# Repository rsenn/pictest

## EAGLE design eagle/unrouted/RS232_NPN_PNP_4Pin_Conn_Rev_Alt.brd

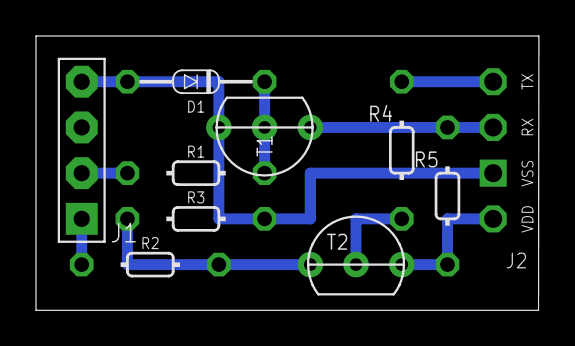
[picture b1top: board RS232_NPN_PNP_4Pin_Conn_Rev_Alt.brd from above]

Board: 2 copper layers, 27.9 x 15.2 mm, 10 parts (0 on the bottom side), 9 nets.

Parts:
D1: 1N414834-7; DO34-7
J1: COMPORT-4PIN-NEW; RS232-4PIN-NEW
J2: PIC-UART-X
R1: 10k; 0202/7
R2: 1k; 0202/7
R3: 4.7k; 0202/7
R4: 10k; 0202/7-V
R5: 1k; 0202/7-V
T1: BC547; TO92-CBE
T2: BC557; TO92-CBE

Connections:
+5V: J2.20, R5.2, T2.E
GND: D1.A, J1.4, J2.19, R3.1, T1.E
unnamed: J2.18, R5.1, T1.C
unnamed: D1.C, R1.1, T1.B
unnamed: J1.2, R1.2
unnamed: J2.17, R4.1
unnamed: R4.2, T2.B
unnamed: R2.1, R3.2, T2.C
unnamed: J1.1, R2.2

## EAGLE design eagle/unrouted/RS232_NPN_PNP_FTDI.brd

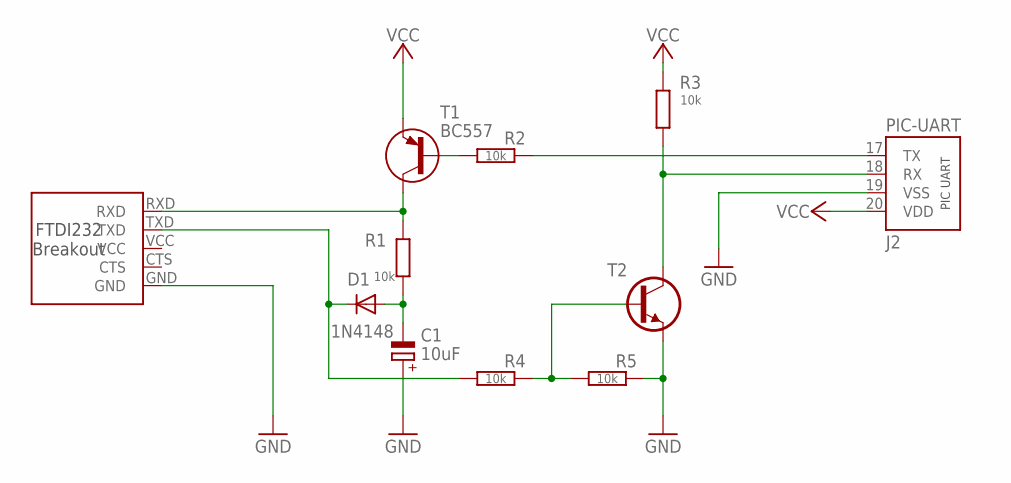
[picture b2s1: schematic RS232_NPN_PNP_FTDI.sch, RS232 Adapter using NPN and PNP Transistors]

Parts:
C1: 10uF; E5-4
D1: 1N4148; DO34-5V
J1: FTDI232-BO-5P-L; FTDI232-BO-5-L
J2: PIC-UART
R1: 10k; 0202/5-V
R2, R3, R5: 10k; 0202/7
R4: 10k; 0202/7-V
T1: BC557; TO92-CBE
T2: BC547; TO92-CBE

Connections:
-12V: C1.-, D1.A, R1.2
GND: C1.+, J1.GND, J2.19 (VSS), R5.1, T2.E
unnamed: R2.2, T1.B
unnamed: R4.1, R5.2, T2.B
RX: J2.18 (RX), R3.2, T2.C
RXD: J1.RXD, R1.1, T1.C
TX: J2.17 (TX), R2.1
TXD: D1.C, J1.TXD, R4.2
VCC: J2.20 (VDD), R3.1, T1.E

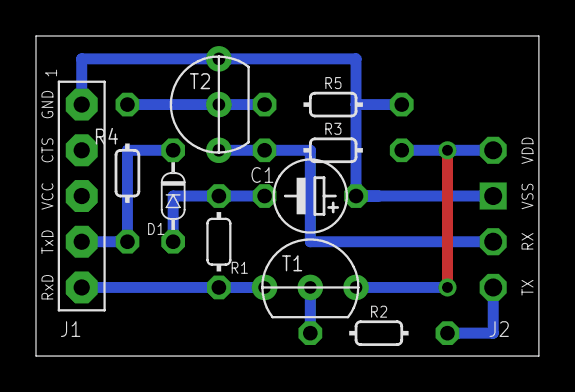
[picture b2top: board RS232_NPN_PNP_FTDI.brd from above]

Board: 2 copper layers, 27.9 x 17.8 mm, 11 parts (0 on the bottom side), 9 nets.

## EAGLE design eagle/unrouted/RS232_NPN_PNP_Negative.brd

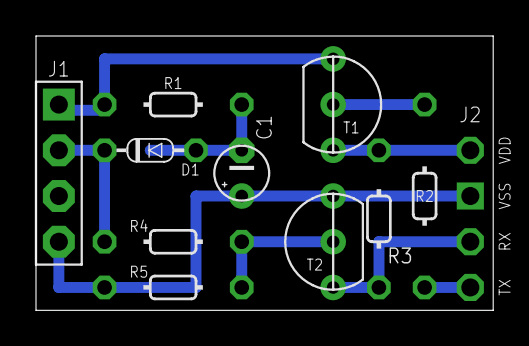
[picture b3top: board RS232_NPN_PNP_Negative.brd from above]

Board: 2 copper layers, 25.4 x 15.2 mm, 11 parts (0 on the bottom side), 9 nets.

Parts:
C1: 10uF; E2,5-3
D1: 1N4148; DO34-5
J1: COMPORT-4PIN-NEW-L; RS232-4PIN-NEW-L
J2: PIC UART (4pin); PIC-UART
R1, R4, R5: 10k; 0202/7
R2: 10k; 0202/10-V
R3: 10k; 0202/7-V
T1: BC557; TO92-CBE
T2: BC547; TO92-CBE

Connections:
-12V: C1.-, D1.A, R1.1
GND: C1.+, J1.4, J2.19, R5.2, T2.E
unnamed: R2.2, T1.B
unnamed: R4.1, R5.1, T2.B
RX: J2.18, R3.1, T2.C
RXD: J1.1, R1.2, T1.C
TX: J2.17, R2.1
TXD: D1.C, J1.2, R4.2
VCC: J2.20, R3.2, T1.E

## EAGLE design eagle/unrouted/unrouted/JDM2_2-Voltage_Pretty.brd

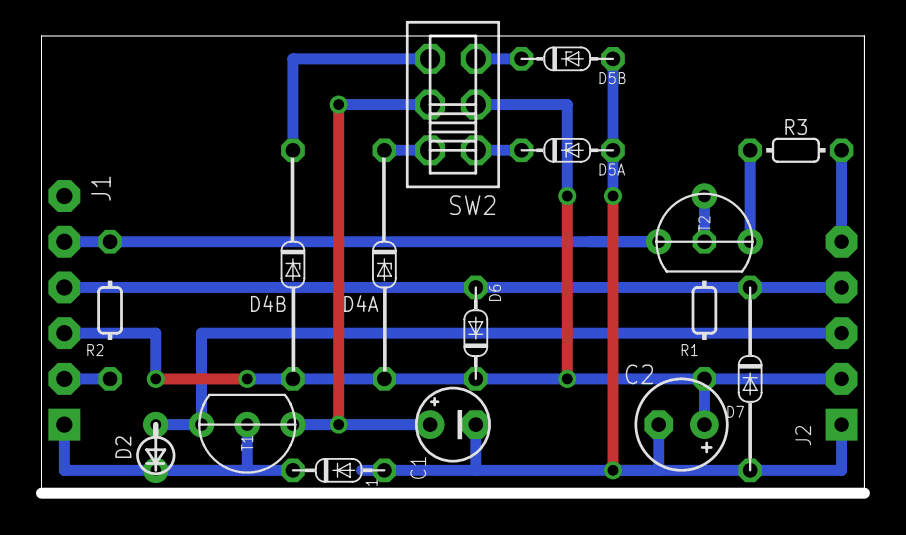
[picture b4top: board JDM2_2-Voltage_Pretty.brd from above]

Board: 2 copper layers, 45.7 x 25.4 mm, 18 parts (0 on the bottom side), 15 nets.

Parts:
C1: 100uF; E2,5-4
C2: 22uF; E2,5-5
D1: 1N4148; DO34-5V
D2: 1N4148; DO34-2,5-A
D4A: Z=5.1V; DO34Z12V
D4B: Z=8.1V; DO34Z12V
D5A: Z=3.3V; DO34Z5
D5B: Z=5.1V; DO34Z5
D6: 1N4148; DO34-5
D7: 1N4148; DO34-10V
J1: COMPORT-6PIN; RS232-6PIN
J2: PIC-ICSPICSP; PIC-ICSP
R1: 10k; 0202/7-V
R2: 1.5k; 0202/7-V
R3: 100; 0202/5
SW2: SL-SW-2P-2T-SV; SLSW-2P2T
T1: BC547; TO92-CBE
T2: BC547; TO92-CBE-A

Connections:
/MCLR: D2.A, J2.3, T1.E
CLK: D6.A, D7.C, J1.4, J2.4
CTS: J1.5, R2.1, T2.C
DATA: R3.2, T2.E
GND: C1.-, C2.-, D1.A, D5A.A, D5B.A, D7.A, J2.1
unnamed: R1.1, T2.B
unnamed: D5A.C, SW2.1
unnamed: D5B.C, SW2.3
unnamed: D4A.C, SW2.4
unnamed: D4B.C, SW2.6
unnamed: J1.2, R2.2
PGD: J2.5, R3.1
TXD: D1.C, D2.C, J1.1, T1.B
VCC: C2.+, D4A.A, D4B.A, D6.C, J1.3, J2.2, R1.2, SW2.2
VPP: C1.+, SW2.5, T1.C

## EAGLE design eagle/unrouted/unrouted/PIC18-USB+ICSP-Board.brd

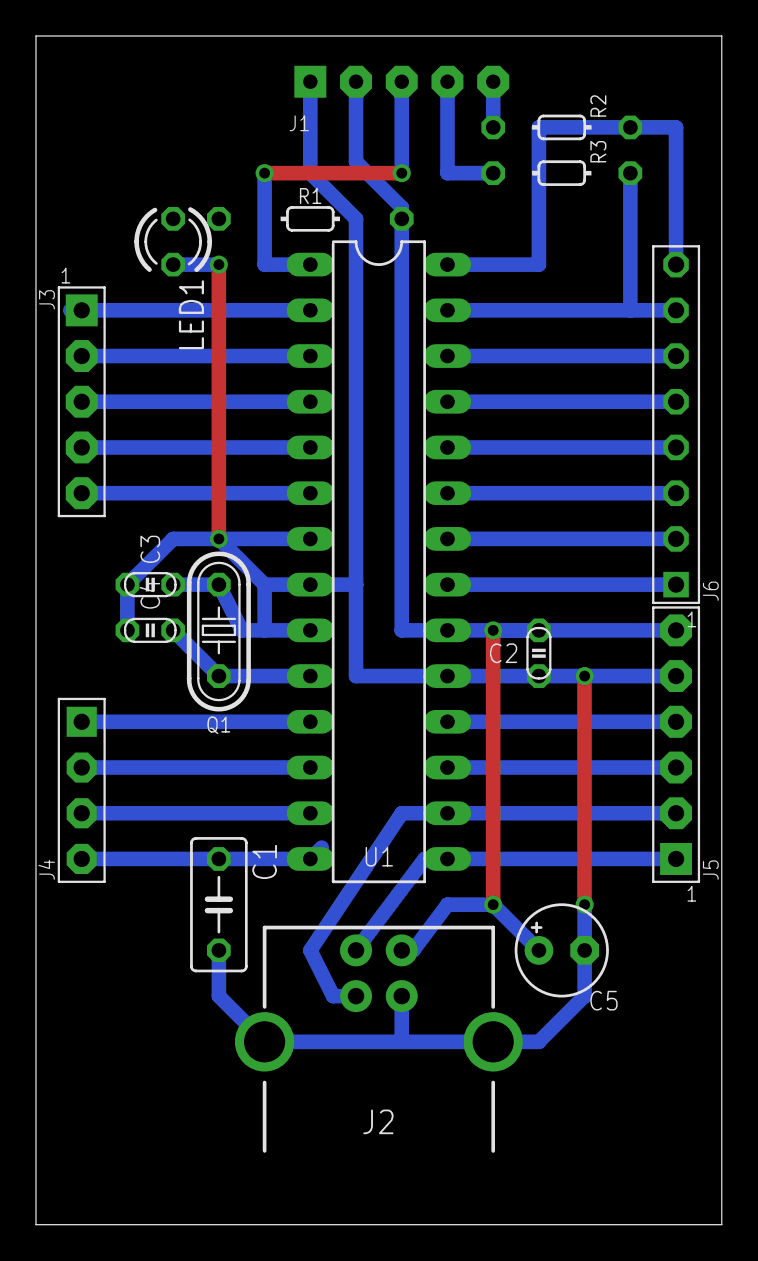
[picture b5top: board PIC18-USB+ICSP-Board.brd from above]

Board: 2 copper layers, 38.1 x 66.0 mm, 17 parts (0 on the bottom side), 30 nets.

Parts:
C1: 330n; C050-030X075
C2: 100n; C025-015X024
C3, C4: 15p; C025-015X024
C5: 100uF; E2,5-5
J1: PIC-ICSP-ICSP; PIC-ICSP
J2: USB-PRINT; USB-B-PRINT
J3: RA[0..4]; CONN-5P-N
J4: RC[0..3]; CONN-4P
J5: PWR+SCI+USB; CONN-6P
J6: RB[0..7]; CONN-8P
LED1: LED3MM
Q1: 20MHz; HC49
R1: 330; 0202/10
R2, R3: 100; 0202/7-V
U1: PIC16F876A-X/SPDIL28-3/V; DIL28-3/V

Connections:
/MCLR: J1.3, U1.1
GND: C1.2, C2.2, C3.2, C4.2, C5.-, J1.1, J2.GND, J5.5, U1.8, U1.19
unnamed: C1.1, J4.4, U1.14
unnamed: J2.D+, J5.2, U1.16
unnamed: J2.D-, J5.1, U1.15
unnamed: LED1.A, R1.1
unnamed: LED1.K, U1.7
unnamed: C3.1, Q1.1, U1.9
unnamed: C4.1, Q1.2, U1.10
unnamed: J6.6, U1.26
unnamed: J6.5, U1.25
unnamed: J6.4, U1.24
unnamed: J6.3, U1.23
unnamed: J6.2, U1.22
unnamed: J6.1, U1.21
unnamed: J3.1, U1.2
unnamed: J5.4, U1.18
unnamed: J5.3, U1.17
unnamed: J3.2, U1.3
unnamed: J3.3, U1.4
unnamed: J3.4, U1.5
unnamed: J3.5, U1.6
unnamed: J4.1, U1.11
unnamed: J4.2, U1.12
unnamed: J4.3, U1.13
unnamed: J1.5, R2.2
unnamed: J1.4, R3.2
PGC: J6.7, R3.1, U1.27
PGD: J6.8, R2.1, U1.28
VDD: C2.1, C5.+, J1.2, J2.VBUS, J5.6, R1.2, U1.20

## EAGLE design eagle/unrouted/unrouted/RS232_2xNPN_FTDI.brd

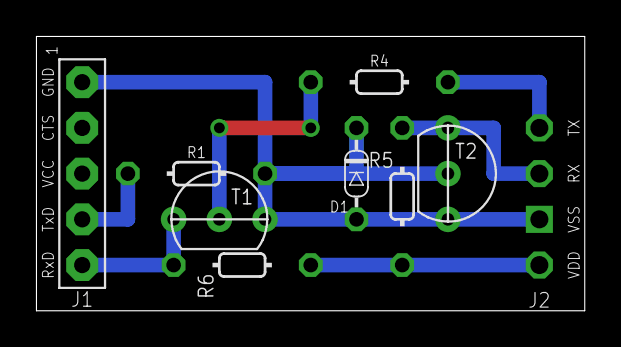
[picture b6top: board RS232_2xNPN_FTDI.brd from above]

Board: 2 copper layers, 30.5 x 15.2 mm, 9 parts (0 on the bottom side), 8 nets.

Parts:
D1: 1N4148; DO34-5V
J1: FTDI232-BO-5P-L; FTDI232-BO-5-L
J2: PIC-UART-X
R1: 4.7k; 0202/7
R4: 10k; 0202/7
R5, R6: 1k; 0202/7-V
T1, T2: BC547; TO92-CBE

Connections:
+5V: J2.20, R5.2, R6.2
GND: D1.A, J1.GND, J2.19, T1.E, T2.E
unnamed: J2.18, R5.1, T2.C
unnamed: D1.C, R1.1, T2.B
unnamed: J1.TXD, R1.2
unnamed: J2.17, R4.1
unnamed: R4.2, T1.B
unnamed: J1.RXD, R6.1, T1.C
